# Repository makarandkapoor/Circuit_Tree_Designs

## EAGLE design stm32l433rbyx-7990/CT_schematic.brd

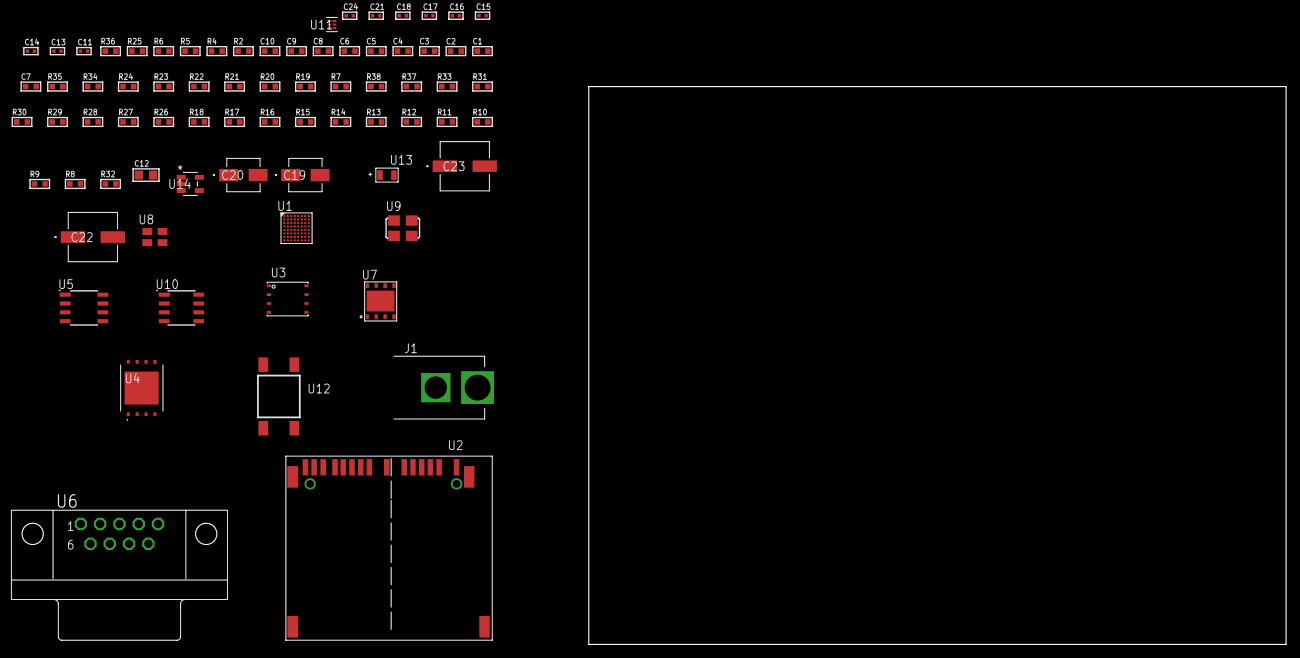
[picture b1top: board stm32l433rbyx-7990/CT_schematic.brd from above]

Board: 2 copper layers, 100.0 x 80.0 mm, 75 parts (0 on the bottom side), 47 nets, no tracks yet.

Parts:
C1, C9: 1e-06; C0603
C2, C3, C4, C5, C6, C10: 1e-07; C0603
C7: 4.7e-06; C0603
C8: 1e-08; C0603
C11, C15, C16, C21: 1e-07; C0402
C12: 1e-05; C0805
C13, C14, C17, C18, C24: 1e-08; C0402
C19: 1e-06; EXV-9B
C20: 2.2e-06; EXV-9B
C22, C23: 0.0001; EXV-9H
J1: PJ-037B; PJ-037B_PACKAGE
R2: 1000.0; R0603
R4: 4700.0; R0603
R5, R6: 2200.0; R0603
R7, R19, R20, R21, R22, R23, R24, R34, R35: 10000.0; R0603
R8, R9, R10, R11, R12, R13, R14, R15, R16, R17, R18, R27, R28, R29, R30, R31, R33: 100000.0; R0603
R25: 120.0; R0603
R26: 470000.0; R0603
R32: 164658.62; R0603
R36: 9100.0; R0603
R37: 680000.0; R0603
R38: 120000.0; R0603
U1: STM32L433RBY6; WLCSP64
U2: 10100565
U3: 24AA512-I/MF; DFN8-S
U4: S25FL128SDPNFI001; WNG008
U5: SN65HVD230D; SOIC-8
U6: 182-009-113R531; 182-009-MALE
U7: SST26VF032B-104I/MF; WFDN-8
U8: ASEK-32.768KHz-ECST; ASEK
U9: ASFL1-25MHZ-NCS; ASFL1
U10: LP2954AIMX/NOPB; LP2954
U11: TPS3895ADRYR; SON-6
U12: 4-1437565-2; SW_4-1437565-2
U13: Q65110A2395; LGM67K-G1J2-24-Z
U14: nc7sz125m5x; NC7SZ125M5X

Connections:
CLK_U1_C8: U1.C8, U8.3
CLK_U1_D8: U1.D8, U9.3
GND: C1.2, C2.2, C3.2, C4.2, C5.2, C6.2, C7.2, C8.2, C9.2, C10.2, C11.2, C12.2, C13.2, C14.2, C15.2, C16.2, C17.2, C18.2, C19.2, C20.2, C21.2, C22.2, C23.2, C24.2, J1.2, R2.2, R7.2, R20.2, R26.2, R33.2, R36.2, R38.2, U1.A7, U1.B1, U1.F8, U1.H2, U1.H8, U2.6, U2.10, U2.12, U2.16, U2.17, U2.20, U2.21, U3.4, U3.7, U4.4, U4.PAD, U5.2, U6.5, U7.4, U7.9, U8.2, U9.2, U10.4, U11.2, U13.C, U14.1, U14.3
NET_U1_A6: R6.1, U1.A6, U3.5
NET_U1_B5: R5.1, U1.B5, U3.6
NET_U1_C5: R7.1, U1.C5
NET_U1_D6: R4.1, U1.D6, U14.4
NET_U1_H4: U12.3, U12.4
NET_U2_1: R10.1, U2.1
NET_U2_2: R9.1, U2.2
NET_U2_18: U2.18, U2.19
NET_U3_1: R19.1, U3.1
NET_U3_2: R20.1, U3.2
NET_U3_3: R21.1, U3.3
NET_U4_3: R22.1, U4.3
NET_U4_7: R24.1, U4.7
NET_U5_6: R25.2, U5.6
NET_U5_8: R26.1, U5.8
NET_U6_2: R25.2, U5.6, U6.2
NET_U6_3: R25.1, U5.7, U6.3
NET_U10_3: R31.1, U10.3
NET_U10_5: R30.1, U10.5
NET_U10_7: R32.2, R33.1, U10.7
NET_U11_1: R35.1, R36.1, U11.1
NET_U11_3: R37.2, R38.1, U11.3
NET_U11_4: R34.1, U11.4, U14.2
NET_U12_1: R2.1, U12.1, U12.2
PROC_CAN1_RX: U1.D3, U5.4
PROC_CAN1_TX: U1.C1, U5.1
PROC_QUADSPI_BK1_IO0: U1.H5, U7.5
PROC_QUADSPI_BK1_IO1: U1.F4, U7.2
PROC_QUADSPI_BK1_IO2: R28.1, U1.H6, U7.3
PROC_QUADSPI_BK1_IO3: R29.1, U1.G5, U7.7
PROC_QUADSPI_BK1_NCS: R27.1, U1.F6, U7.1
PROC_QUADSPI_CLK: U1.G6, U7.6
PROC_SDMMC1_CK: R8.1, U1.A3, U2.8
PROC_SDMMC1_D0: R11.1, U1.F3, U2.4
PROC_SDMMC1_D1: R12.1, U1.E2, U2.3
PROC_SDMMC1_D2: R13.1, U1.C3, U2.15
PROC_SDMMC1_D3: R14.1, U1.B3, U2.14
PROC_SDMMC1_D4: R15.1, U1.C6, U2.13
PROC_SDMMC1_D5: R16.1, U1.B6, U2.11
PROC_SDMMC1_D6: R17.1, U1.F1, U2.7
PROC_SDMMC1_D7: R18.1, U1.E1, U2.5
PROC_SPI1_NSS: R23.1, U4.1
VCC_S1_6V4: C19.1, C22.1, C23.1, J1.1, R31.2, U10.8
VCC_TIER1_3V3: C1.1, C2.1, C3.1, C4.1, C5.1, C6.1, C7.1, C8.1, C9.1, C10.1, C11.1, C12.1, C13.1, C14.1, C15.1, C16.1, C17.1, C18.1, C20.1, C21.1, C24.1, R4.2, R5.2, R6.2, R8.2, R9.2, R10.2, R11.2, R12.2, R13.2, R14.2, R15.2, R16.2, R17.2, R18.2, R19.2, R21.2, R22.2, R23.2, R24.2, R27.2, R28.2, R29.2, R30.2, R32.1, R34.2, R35.2, R37.1, U1.A1, U1.A8, U1.B7, U1.G8, U1.H1, U1.H7, U2.9, U3.8, U4.8, U5.3, U7.8, U8.4, U9.4, U10.1, U11.6, U14.5

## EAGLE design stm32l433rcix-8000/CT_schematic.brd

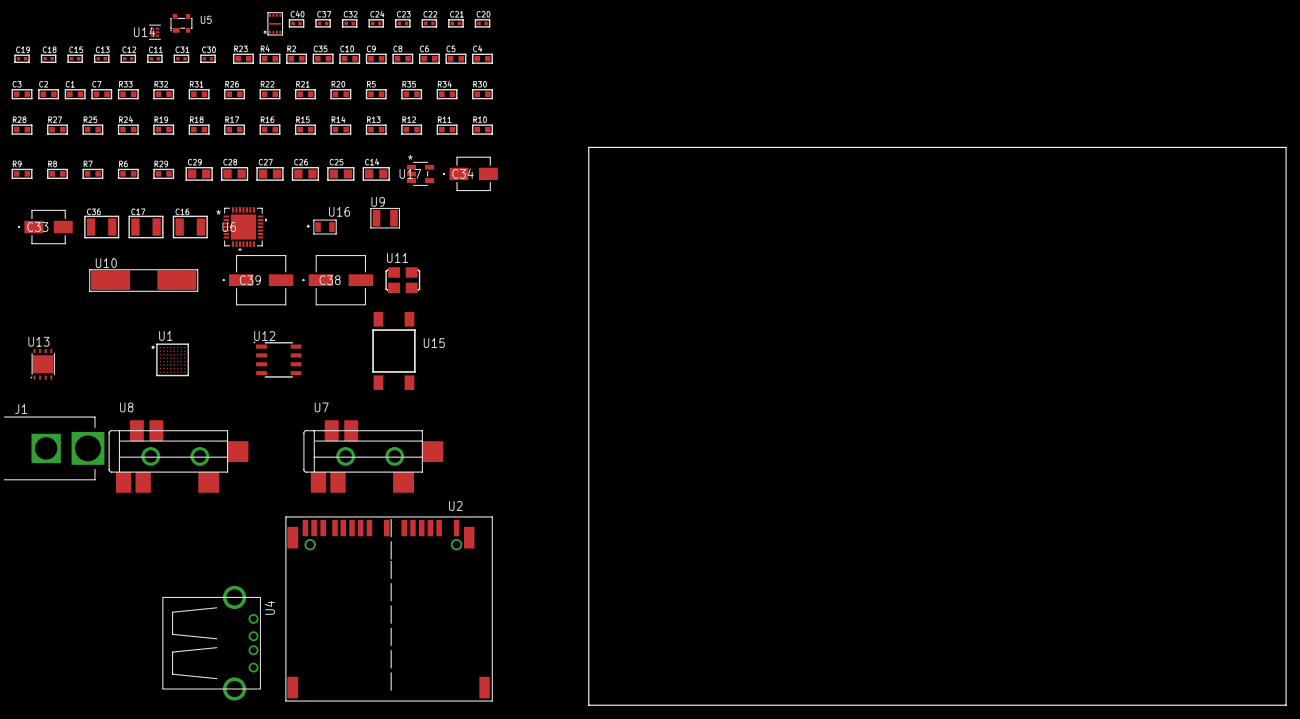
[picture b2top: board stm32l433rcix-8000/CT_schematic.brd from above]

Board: 2 copper layers, 100.0 x 80.0 mm, 91 parts (0 on the bottom side), 49 nets, no tracks yet.

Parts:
C1, C9, C35: 1e-06; C0603
C2, C3, C4, C5, C6, C10: 1e-07; C0603
C7: 4.7e-06; C0603
C8: 1e-08; C0603
C11, C12: 1e-11; C0402
C13, C15, C20, C21, C22, C23, C24, C37: 1e-07; C0402
C14, C25, C26, C27, C28, C29: 1e-05; C0805
C16, C17: 2.2e-05; C1210
C18, C19: 1e-09; C0402
C30, C31: 2.2e-11; C0402
C32, C40: 1e-08; C0402
C33: 1e-06; EXV-9B
C34: 2.2e-06; EXV-9B
C36: 1e-05; C1210
C38, C39: 0.0001; EXV-9H
J1: PJ-037B; PJ-037B_PACKAGE
R2: 1000.0; R0603
R4: 4700.0; R0603
R5, R31, R32: 10000.0; R0603
R6, R7, R8, R9, R10, R11, R12, R13, R14, R15, R16, R17, R18, R19, R24, R25, R27, R28, R30: 100000.0; R0603
R20, R21, R22, R26: 47000.0; R0603
R23: 680.0; R0603
R29: 153694.38; R0603
R33: 82000.0; R0603
R34: 300000.0; R0603
R35: 120000.0; R0603
U1: STM32L433RCI6; UFBGA64
U2: 10100565
U3: SST26WF080BT-104I/NP; USON-8
U4: 61400416021; USB-A-H
U5: prtr5v0u2ax; SOT143B
U6: WM8731CLSEFL; QFN-28
U7, U8: SJ-43515TS-SMT-TR
U9: ABS07-32.768KHZ-7-T
U10: ABLS-12.288MHZ-B4-T
U11: ASFL1-25MHZ-NCS; ASFL1
U12: LP2954AIMX/NOPB; LP2954
U13: LP2951ACSDX/NOPB; WSON-8
U14: TPS3895ADRYR; SON-6
U15: 4-1437565-2; SW_4-1437565-2
U16: Q65110A2395; LGM67K-G1J2-24-Z
U17: nc7sz125m5x; NC7SZ125M5X

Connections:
CLK_CRYSTAL_U1_A1: C11.1, U1.A1, U9.1
CLK_CRYSTAL_U1_B1: C12.1, U1.B1, U9.2
CLK_CRYSTAL_U6_1: C30.1, U6.1, U10.1
CLK_CRYSTAL_U6_2: C31.1, U6.2, U10.2
CLK_U1_C1: U1.C1, U11.3
GND: C1.2, C2.2, C3.2, C4.2, C5.2, C6.2, C7.2, C8.2, C9.2, C10.2, C11.2, C12.2, C13.2, C14.2, C15.2, C19.2, C20.2, C21.2, C22.2, C23.2, C24.2, C25.2, C26.2, C27.2, C28.2, C29.2, C30.2, C31.2, C32.2, C33.2, C34.2, C35.2, C36.2, C37.2, C38.2, C39.2, C40.2, J1.2, R2.2, R5.2, R20.2, R21.2, R22.2, R27.2, R30.2, R33.2, R35.2, U1.C2, U1.D4, U1.D5, U1.D6, U1.F1, U2.6, U2.10, U2.12, U2.16, U2.17, U2.20, U2.21, U3.4, U3.9, U4.4, U4.5, U4.6, U5.1, U6.4, U6.15, U6.19, U6.25, U6.26, U6.29, U7.1, U8.1, U11.2, U12.4, U13.3, U13.4, U13.PAD, U14.2, U16.C, U17.1, U17.3
NET_U1_B4: R5.1, U1.B4
NET_U1_E1: R4.1, U1.E1, U17.4
NET_U1_H8: U15.3, U15.4
NET_U2_1: R8.1, U2.1
NET_U2_2: R7.1, U2.2
NET_U2_18: U2.18, U2.19
NET_U5_4: U4.1, U5.4
NET_U6_20: C24.1, C29.1, U6.20
NET_U7_2: C17.1, R21.1, U7.2
NET_U7_5: C16.1, R20.1, U7.5
NET_U8_5: C18.1, C19.1, R22.1, R23.1, U8.5
NET_U12_3: R25.1, U12.3
NET_U12_5: R24.1, U12.5
NET_U12_7: R26.2, R27.1, U12.7
NET_U13_5: R28.1, U13.5
NET_U13_7: R29.2, R30.1, U13.7
NET_U14_1: R32.1, R33.1, U14.1
NET_U14_3: R34.2, R35.1, U14.3
NET_U14_4: R31.1, U14.4, U17.2
NET_U15_1: R2.1, U15.1, U15.2
PROC_QUADSPI_BK1_IO0: U1.G5, U3.5
PROC_QUADSPI_BK1_IO1: U1.F5, U3.2
PROC_QUADSPI_BK1_IO2: R18.1, U1.H4, U3.3
PROC_QUADSPI_BK1_IO3: R19.1, U1.G4, U3.7
PROC_QUADSPI_BK1_NCS: R17.1, U1.F3, U3.1
PROC_QUADSPI_CLK: U1.G3, U3.6
PROC_SAI1_FS_A: U1.C7, U6.9, U6.11
PROC_SAI1_SCK_A: U1.D7, U6.7
PROC_SAI1_SD_A: U1.C6, U6.8
PROC_SDMMC1_CK: R6.1, U1.C5, U2.8
PROC_SDMMC1_D0: R9.1, U1.E8, U2.4
PROC_SDMMC1_D1: R10.1, U1.D8, U2.3
PROC_SDMMC1_D2: R11.1, U1.B7, U2.15
PROC_SDMMC1_D3: R12.1, U1.B6, U2.14
PROC_SDMMC1_D4: R13.1, U1.B3, U2.13
PROC_SDMMC1_D5: R14.1, U1.A3, U2.11
PROC_SDMMC1_D6: R15.1, U1.F6, U2.7
PROC_SDMMC1_D7: R16.1, U1.E7, U2.5
PROC_USB_DM: U1.C8, U4.2, U5.3
PROC_USB_DP: U1.B8, U4.3, U5.2
VCC_S1_11V0: C33.1, C35.1, C38.1, C39.1, J1.1, R25.2, U12.8, U13.8
VCC_TIER1_1V8: C1.1, C2.1, C3.1, C4.1, C5.1, C6.1, C7.1, C13.1, C14.1, C15.1, C20.1, C21.1, C22.1, C23.1, C25.1, C26.1, C27.1, C28.1, C34.1, C37.1, C40.1, R4.2, R6.2, R7.2, R8.2, R9.2, R10.2, R11.2, R12.2, R13.2, R14.2, R15.2, R16.2, R17.2, R18.2, R19.2, R24.2, R26.1, R31.2, R32.2, R34.1, U1.B2, U1.D2, U1.E4, U1.E6, U2.9, U3.8, U6.3, U6.5, U6.12, U6.18, U12.1, U14.6, U17.5
VCC_TIER1_3V3: C8.1, C9.1, C10.1, C32.1, C36.1, R28.2, R29.1, U1.E5, U1.H1, U11.4, U13.1

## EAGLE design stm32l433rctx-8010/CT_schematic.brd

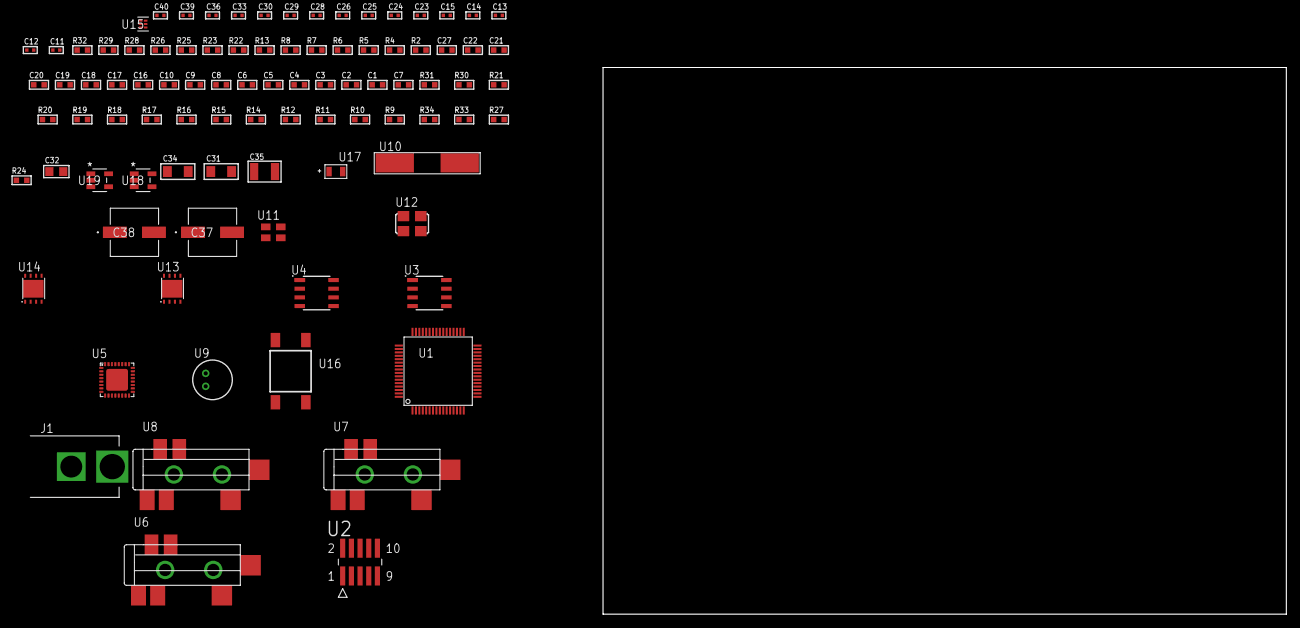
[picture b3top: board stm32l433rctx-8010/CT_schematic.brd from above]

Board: 2 copper layers, 100.0 x 80.0 mm, 92 parts (0 on the bottom side), 54 nets, no tracks yet.

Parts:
C1, C9, C16, C17, C18, C19, C20, C21, C22, C27: 1e-06; C0603
C2, C3, C4, C5, C6, C10: 1e-07; C0603
C7: 4.7e-06; C0603
C8: 1e-08; C0603
C11, C12: 1e-11; C0402
C13, C23, C24, C25, C26, C36: 1e-07; C0402
C14, C15, C28, C29, C30, C33, C39, C40: 1e-08; C0402
C31, C34: 1e-05; C1206
C32: 1e-05; C0805
C35: 1e-05; C1210
C37, C38: 0.0001; EXV-9H
J1: PJ-037B; PJ-037B_PACKAGE
R2, R26, R29: 1000.0; R0603
R4: 4700.0; R0603
R5, R6, R7, R8: 2200.0; R0603
R9, R10, R11, R12, R14, R15, R16, R17, R18, R19, R20, R21, R30, R31: 10000.0; R0603
R13: 5.0; R0603
R22, R23: 1270.0; R0603
R24, R27: 100000.0; R0603
R25: 200.0; R0603
R28: 2231.0; R0603
R32: 9100.0; R0603
R33: 680000.0; R0603
R34: 120000.0; R0603
U1: STM32L433RCT6; LQFP64
U2: FTSH-105-01-L-DV-K; SAMTEC_FTSH-105-01-L-DV-K
U3, U4: AT24C02D-SSHM-T; AT24C02D
U5: SGTL5000XNAA3; QFN-32
U6, U7, U8: SJ-43515TS-SMT-TR
U9: WM-64PCT; WM-64PC
U10: ABLS-25.000MHZ-B2F-T
U11: ASEK-32.768KHz-ECST; ASEK
U12: ASFL-24.57MHZ-NCS; ASFL1
U13, U14: LP3878SDX-ADJ/NOPB; WSON-8
U15: TPS3895ADRYR; SON-6
U16: 4-1437565-2; SW_4-1437565-2
U17: Q65110A2395; LGM67K-G1J2-24-Z
U18, U19: nc7sz125m5x; NC7SZ125M5X

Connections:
CLK_CRYSTAL_U1_5: C11.1, U1.5, U10.1
CLK_CRYSTAL_U1_6: C12.1, U1.6, U10.2
CLK_U1_3: U1.3, U11.3
CLK_U5_21: U5.21, U12.3
GND: C1.2, C2.2, C3.2, C4.2, C5.2, C6.2, C7.2, C8.2, C9.2, C10.2, C11.2, C12.2, C13.2, C14.2, C15.2, C23.2, C24.2, C25.2, C26.2, C27.2, C28.2, C29.2, C30.2, C31.2, C32.2, C33.2, C34.2, C35.2, C36.2, C37.2, C38.2, C39.2, C40.2, J1.2, R2.2, R9.2, R13.2, R14.2, R16.2, R17.2, R18.2, R20.2, R21.2, R23.2, R26.2, R29.2, R32.2, R34.2, U1.12, U1.18, U1.31, U1.47, U1.63, U2.3, U2.5, U3.4, U4.4, U5.1, U5.3, U5.7, U5.EXP, U7.1, U8.1, U9.2, U11.2, U12.2, U13.3, U13.PAD, U14.3, U14.PAD, U15.2, U17.C, U18.2, U18.3, U19.1, U19.3
NET_U1_7: R4.1, U1.7, U19.4
NET_U1_29: R7.1, U1.29, U4.6
NET_U1_30: R8.1, U1.30, U4.5
NET_U1_42: R5.1, U1.42, U3.6
NET_U1_43: R6.1, U1.43, U3.5
NET_U1_60: R9.1, U1.60
NET_U1_62: U16.3, U16.4
NET_U2_9: R13.1, U2.9
NET_U3_1: R15.1, U3.1
NET_U3_2: R16.1, U3.2
NET_U3_3: R17.1, U3.3
NET_U3_7: R14.1, U3.7
NET_U4_1: R19.1, U4.1
NET_U4_2: R20.1, U4.2
NET_U4_3: R21.1, U4.3
NET_U4_7: R18.1, U4.7
NET_U5_10: C26.1, U5.10
NET_U5_29: R22.1, U5.29
NET_U5_31: R23.1, U5.31
NET_U6_1: U5.4, U6.1
NET_U6_2: U5.2, U6.2
NET_U6_5: U5.6, U6.5
NET_U7_2: C17.1, U7.2
NET_U7_5: C16.1, U7.5
NET_U8_2: C19.1, C20.1, U8.2
NET_U8_5: C18.1, U8.5
NET_U8_13: C19.2, C20.2
NET_U9_1: C21.1, C22.1, C27.1, U5.16, U9.1
NET_U9_15: C21.2, C22.2
NET_U13_1: C30.1, U13.1
NET_U13_6: R25.2, R26.1, U13.6
NET_U13_8: R24.1, U13.8
NET_U14_1: C33.1, U14.1
NET_U14_6: R28.2, R29.1, U14.6
NET_U14_8: R27.1, U14.8
NET_U15_1: R31.1, R32.1, U15.1
NET_U15_3: R33.2, R34.1, U15.3
NET_U15_4: R30.1, U15.4, U18.4, U19.2
NET_U16_1: R2.1, U16.1, U16.2
PROC_SAI1_FS_A: U1.33, U5.23
PROC_SAI1_SCK_A: U1.34, U5.24
PROC_SAI1_SD_A: U1.11, U5.26
PROC_SYS_JTCK_SWCLK: R11.1, U1.49, U2.4
PROC_SYS_JTDO_SWO: U1.55, U2.6
PROC_SYS_JTMS_SWDIO: R12.1, U1.46, U2.2
RST_OUT_U2_JTAG_RST_B: R10.1, U2.10, U18.1
VCC_S1_10V8: C31.1, C34.1, C37.1, C38.1, J1.1, R24.2, R27.2, U13.4, U14.4
VCC_TIER1_1V2: C23.1, C32.1, R25.1, U5.30, U13.5
VCC_TIER1_3V3: C1.1, C2.1, C3.1, C4.1, C5.1, C6.1, C7.1, C8.1, C9.1, C10.1, C13.1, C14.1, C15.1, C24.1, C25.1, C28.1, C29.1, C35.1, C36.1, C39.1, C40.1, R4.2, R5.2, R6.2, R7.2, R8.2, R10.2, R11.2, R12.2, R15.2, R19.2, R22.2, R28.1, R30.2, R31.2, R33.1, U1.1, U1.13, U1.19, U1.32, U1.48, U1.64, U2.1, U3.8, U4.8, U5.5, U5.20, U11.4, U12.4, U14.5, U15.6, U18.5, U19.5

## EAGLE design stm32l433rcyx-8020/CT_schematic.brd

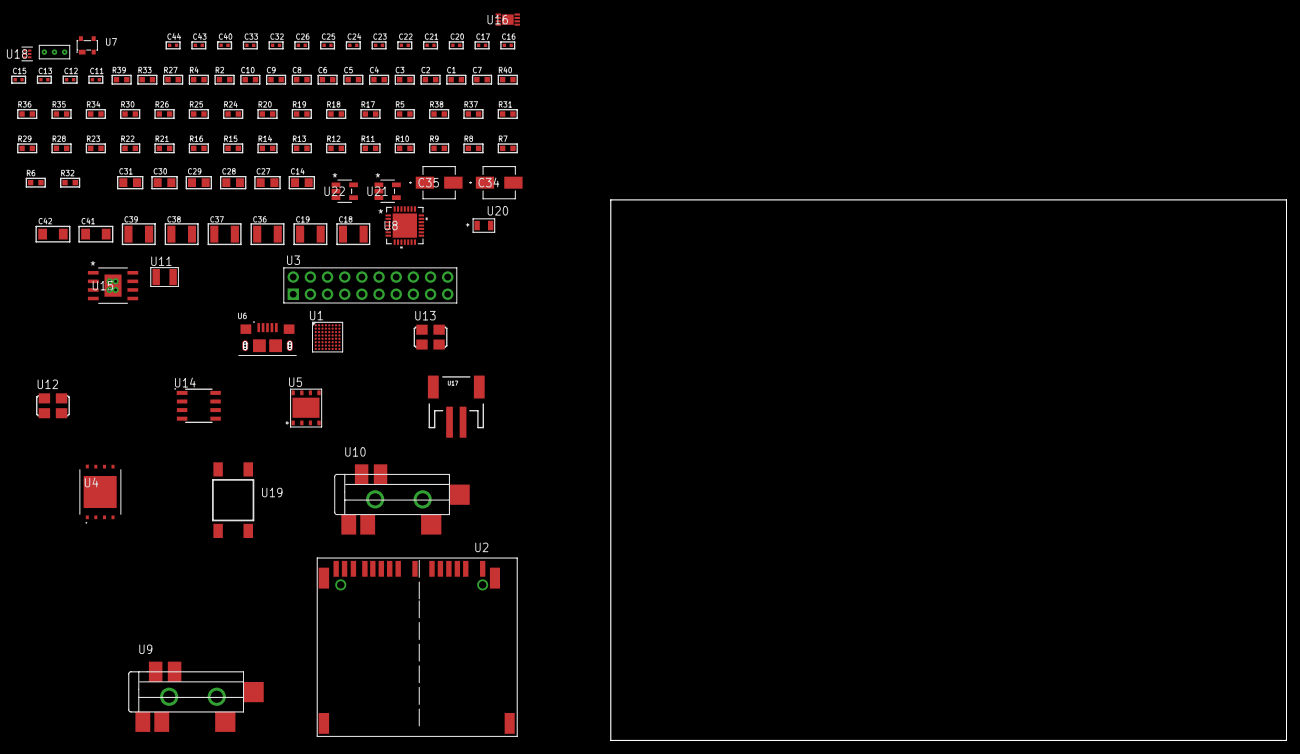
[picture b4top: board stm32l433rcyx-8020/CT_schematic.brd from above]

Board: 2 copper layers, 105 parts (0 on the bottom side), 61 nets, no tracks yet.

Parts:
C1, C9: 1e-06; C0603
C2, C3, C4, C5, C6, C10: 1e-07; C0603
C7: 4.7e-06; C0603
C8: 1e-08; C0603
C11, C12: 1e-11; C0402
C13, C15, C17, C22, C23, C24, C25, C26, C40: 1e-07; C0402
C14, C27, C28, C29, C30, C31: 1e-05; C0805
C16, C32, C33, C43, C44: 1e-08; C0402
C18, C19: 2.2e-05; C1210
C20, C21: 1e-09; C0402
C34: 1e-06; EXV-9B
C35: 2.2e-06; EXV-9B
C36, C37, C38, C39: 1e-05; C1210
C41, C42: 1e-05; C1206
R2: 1000.0; R0603
R4: 4700.0; R0603
R5, R17, R18, R19, R20, R34, R35, R40: 10000.0; R0603
R6, R7, R8, R9, R10, R11, R12, R13, R14, R15, R16, R21, R22, R23, R28, R29, R31: 100000.0; R0603
R24, R25, R26, R30: 47000.0; R0603
R27: 680.0; R0603
R32: 4031.5447154472; R0603
R33: 2200.0; R0603
R36: 82000.0; R0603
R37: 300000.0; R0603
R38: 120000.0; R0603
R39: 2000.0; R0603
U1: STM32L433RCY6; WLCSP64
U2: 10100565
U3: TST-110-05-T-D-RA
U4: S25FL128SDPNFI001; WNG008
U5: SST26WF016B-104I/MF; WFDN-8
U6: 10118193-0001LF; FCI_10118193-0001LF
U7: prtr5v0u2ax; SOT143B
U8: WM8731CLSEFL; QFN-28
U9, U10: SJ-43515TS-SMT-TR
U11: ABS07-32.768KHZ-7-T
U12: ASFL1-12.288MHZ-EC-T; ASFL1
U13: ASFL1-25MHZ-NCS; ASFL1
U14: LP2954AIMX/NOPB; LP2954
U15: MIC5234YME; SOIC-8_EP
U16: MCP73831T-2ACI/MC; DFN8_2X3MC
U17: S2B-PH-SM4-TB(LF)(SN); JST-2-SMD
U18: TPS3895ADRYR; SON-6
U19: 4-1437565-2; SW_4-1437565-2
U20: Q65110A2395; LGM67K-G1J2-24-Z
U21, U22: nc7sz125m5x; NC7SZ125M5X
U23: Dummy; DUMMY_PACKAGE_231

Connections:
CLK_CRYSTAL_U1_C7: C11.1, U1.C7, U11.1
CLK_CRYSTAL_U1_C8: C12.1, U1.C8, U11.2
CLK_U1_D8: U1.D8, U13.3
CLK_U8_1: U8.1, U12.3
GND: C1.2, C2.2, C3.2, C4.2, C5.2, C6.2, C7.2, C8.2, C9.2, C10.2, C11.2, C12.2, C13.2, C14.2, C15.2, C16.2, C17.2, C21.2, C22.2, C23.2, C24.2, C25.2, C26.2, C27.2, C28.2, C29.2, C30.2, C31.2, C32.2, C33.2, C34.2, C35.2, C36.2, C37.2, C38.2, C39.2, C40.2, C41.2, C42.2, C43.2, C44.2, R2.2, R5.2, R24.2, R25.2, R26.2, R31.2, R33.2, R36.2, R38.2, R39.2, U1.A7, U1.B1, U1.F8, U1.H2, U1.H8, U2.6, U2.10, U2.12, U2.16, U2.17, U2.20, U2.21, U3.4, U3.6, U3.8, U3.10, U3.12, U3.14, U3.16, U3.18, U3.20, U4.4, U4.PAD, U5.4, U5.9, U6.5, U6.6, U6.7, U6.8, U6.9, U7.1, U8.4, U8.15, U8.19, U8.25, U8.26, U8.29, U9.1, U10.1, U12.2, U13.2, U14.4, U15.7, U15.EPAD, U16.6, U16.9, U17.2, U18.2, U20.C, U21.2, U21.3, U22.1, U22.3, U23.1
INPUT_USBPOWER_5V: C41.1, R40.2, U6.1, U7.4, U16.1, U16.2
NET_U1_C5: R5.1, U1.C5
NET_U1_D6: R4.1, U1.D6, U22.4
NET_U1_H4: U19.3, U19.4
NET_U2_1: R8.1, U2.1
NET_U2_2: R7.1, U2.2
NET_U2_18: U2.18, U2.19
NET_U4_3: R18.1, U4.3
NET_U4_7: R20.1, U4.7
NET_U8_20: C26.1, C31.1, U8.20
NET_U9_2: C19.1, R25.1, U9.2
NET_U9_5: C18.1, R24.1, U9.5
NET_U10_5: C20.1, C21.1, R26.1, R27.1, U10.5
NET_U14_3: R29.1, U14.3
NET_U14_5: R28.1, U14.5
NET_U14_7: R30.2, R31.1, U14.7
NET_U15_4: R32.2, R33.1, U15.4
NET_U16_5: R40.1, U16.5
NET_U16_8: R39.1, U16.8
NET_U18_1: R35.1, R36.1, U18.1
NET_U18_3: R37.2, R38.1, U18.3
NET_U18_4: R34.1, U18.4, U21.4, U22.2
NET_U19_1: R2.1, U19.1, U19.2
PROC_PB7: U1.A6, U23.3
PROC_PD2: U1.A4, U23.2
PROC_QUADSPI_BK1_IO0: U1.H5, U5.5
PROC_QUADSPI_BK1_IO1: U1.F4, U5.2
PROC_QUADSPI_BK1_IO2: R22.1, U1.H6, U5.3
PROC_QUADSPI_BK1_IO3: R23.1, U1.G5, U5.7
PROC_QUADSPI_BK1_NCS: R21.1, U1.F6, U5.1
PROC_QUADSPI_CLK: U1.G6, U5.6
PROC_SAI1_FS_A: U1.D1, U8.9, U8.11
PROC_SAI1_SCK_A: U1.E3, U8.7
PROC_SAI1_SD_A: U1.D2, U8.8
PROC_SDMMC1_CK: R6.1, U1.A3, U2.8
PROC_SDMMC1_D0: R9.1, U1.F3, U2.4
PROC_SDMMC1_D1: R10.1, U1.E2, U2.3
PROC_SDMMC1_D2: R11.1, U1.C3, U2.15
PROC_SDMMC1_D3: R12.1, U1.B3, U2.14
PROC_SDMMC1_D4: R13.1, U1.C6, U2.13
PROC_SDMMC1_D5: R14.1, U1.B6, U2.11
PROC_SDMMC1_D6: R15.1, U1.F1, U2.7
PROC_SDMMC1_D7: R16.1, U1.E1, U2.5
PROC_SPI1_MISO: U1.B4, U4.2
PROC_SPI1_MOSI: U1.C4, U4.5
PROC_SPI1_NSS: R19.1, U1.A2, U4.1
PROC_SPI1_SCK: U1.F5, U4.6
PROC_SYS_JTCK_SWCLK: U1.B2, U3.9
PROC_SYS_JTDO_SWO: U1.A5, U3.13
PROC_SYS_JTMS_SWDIO: U1.C2, U3.7
PROC_USB_DM: U1.D3, U6.2, U7.3
PROC_USB_DP: U1.C1, U6.3, U7.2
RST_OUT_U3_SRESET_B: R17.1, U3.15, U21.1
VCC_S1_3V7: C34.1, C36.1, C37.1, C42.1, R29.2, U14.8, U15.5, U15.8, U16.3, U16.4, U17.1
VCC_TIER1_1V8: C1.1, C2.1, C3.1, C4.1, C5.1, C6.1, C7.1, C8.1, C9.1, C13.1, C14.1, C15.1, C16.1, C17.1, C22.1, C23.1, C24.1, C25.1, C27.1, C28.1, C29.1, C30.1, C35.1, C40.1, C43.1, C44.1, R4.2, R6.2, R7.2, R8.2, R9.2, R10.2, R11.2, R12.2, R13.2, R14.2, R15.2, R16.2, R17.2, R18.2, R19.2, R20.2, R21.2, R22.2, R23.2, R28.2, R30.1, R34.2, R35.2, R37.1, U1.A8, U1.B7, U1.G8, U1.H1, U1.H7, U2.9, U3.1, U4.8, U5.8, U8.3, U8.5, U8.12, U8.18, U14.1, U18.6, U21.5, U22.5
VCC_TIER1_3V3: C10.1, C32.1, C33.1, C38.1, C39.1, R32.1, U1.A1, U12.4, U13.4, U15.1

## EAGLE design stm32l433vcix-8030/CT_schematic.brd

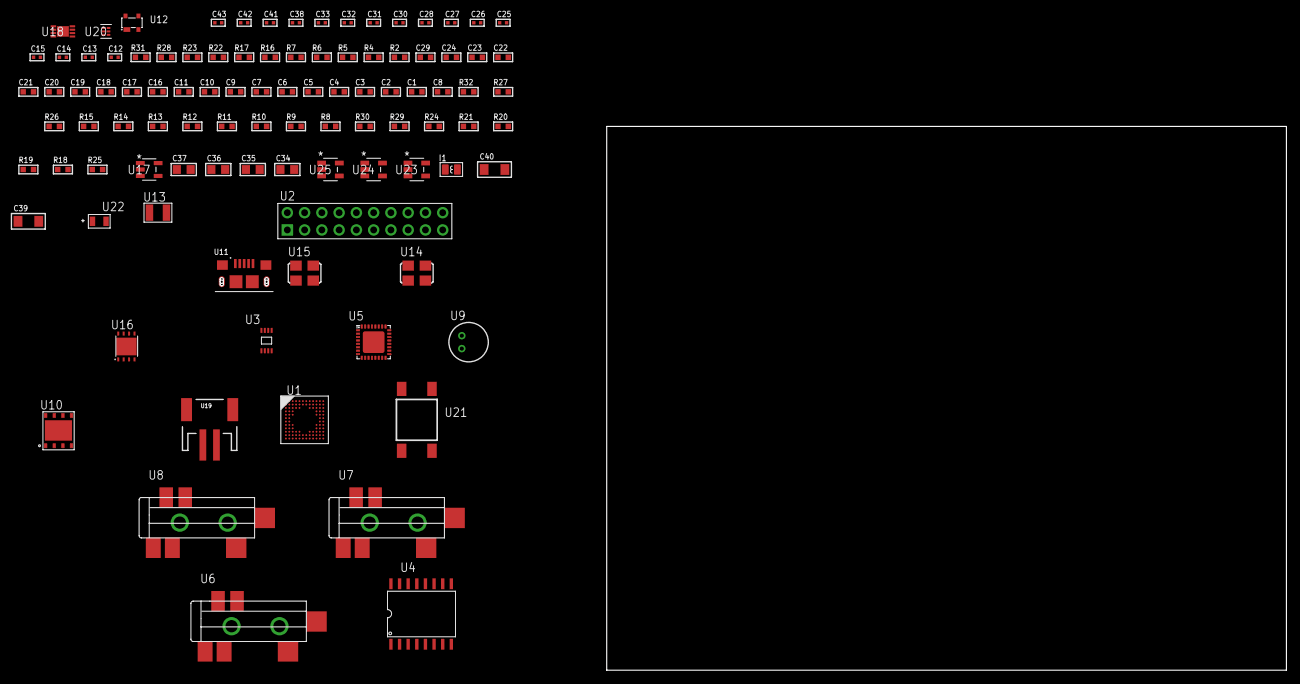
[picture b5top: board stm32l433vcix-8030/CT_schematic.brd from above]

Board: 2 copper layers, 99 parts (0 on the bottom side), 63 nets, no tracks yet.

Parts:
C1, C11, C16, C17, C18, C19, C20, C21, C22, C23, C24, C29: 1e-06; C0603
C2, C3, C4, C5, C6, C7, C9: 1e-07; C0603
C8: 4.7e-06; C0603
C10: 1e-08; C0603
C12, C13: 1e-11; C0402
C14, C25, C26, C27, C28, C30, C38: 1e-07; C0402
C15, C31, C32, C33, C41, C42, C43: 1e-08; C0402
C34, C35, C36, C37: 1e-05; C0805
C39, C40: 1e-05; C1206
I1: 1.5e-06; L0806
R2, R23: 1000.0; R0603
R4, R5: 4700.0; R0603
R6, R7: 2200.0; R0603
R8, R9, R10, R11, R12, R13, R14, R15, R26, R27, R32: 10000.0; R0603
R16, R17: 1270.0; R0603
R18, R19, R20, R21: 100000.0; R0603
R22: 200.0; R0603
R24: 220000.0; R0603
R25: 1000000.0; R0603
R28: 9100.0; R0603
R29: 680000.0; R0603
R30: 120000.0; R0603
R31: 2000.0; R0603
U1: STM32L433VCI6; UFBGA100
U2: TST-110-05-T-D-RA
U3: 24AA32AT-I/MNY; TDFN-8/6MM
U4: S25FL128SDSMFI000
U5: SGTL5000XNAA3; QFN-32
U6, U7, U8: SJ-43515TS-SMT-TR
U9: WM-64PCT; WM-64PC
U10: SST26VF064B-104I/MF; WFDN-8
U11: 10118193-0001LF; FCI_10118193-0001LF
U12: prtr5v0u2ax; SOT143B
U13: ABS07-32.768KHZ-7-T
U14: ASFL-24.57MHZ-NCS; ASFL1
U15: ASFL1-25MHZ-NCS; ASFL1
U16: LP3878SDX-ADJ/NOPB; WSON-8
U17: ltc3406es5; TSOT-23-5
U18: MCP73831T-2ACI/MC; DFN8_2X3MC
U19: S2B-PH-SM4-TB(LF)(SN); JST-2-SMD
U20: TPS3895ADRYR; SON-6
U21: 4-1437565-2; SW_4-1437565-2
U22: Q65110A2395; LGM67K-G1J2-24-Z
U23, U24, U25: nc7sz125m5x; NC7SZ125M5X

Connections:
CLK_CRYSTAL_U1_D1: C12.1, U1.D1, U13.1
CLK_CRYSTAL_U1_E1: C13.1, U1.E1, U13.2
CLK_U1_F1: U1.F1, U15.3
CLK_U5_21: U5.21, U14.3
GND: C1.2, C2.2, C3.2, C4.2, C5.2, C6.2, C7.2, C8.2, C9.2, C10.2, C11.2, C12.2, C13.2, C14.2, C15.2, C16.2, C17.2, C25.2, C26.2, C27.2, C28.2, C29.2, C30.2, C31.2, C32.2, C33.2, C34.2, C35.2, C36.2, C37.1, C37.2, C38.2, C39.2, C40.2, C41.2, C42.2, C43.2, R2.2, R8.2, R11.2, R12.2, R17.2, R23.2, R24.2, R28.2, R30.2, R31.2, U1.D3, U1.E3, U1.F2, U1.F11, U1.F12, U1.J1, U1.K1, U2.4, U2.6, U2.8, U2.10, U2.12, U2.14, U2.16, U2.18, U2.20, U3.4, U3.7, U4.10, U5.1, U5.3, U5.7, U5.EXP, U7.1, U8.1, U9.2, U10.4, U10.9, U11.5, U11.6, U11.7, U11.8, U11.9, U12.1, U14.2, U15.2, U16.3, U16.PAD, U17.2, U18.6, U18.9, U19.2, U20.2, U22.C, U23.2, U23.3, U24.1, U24.3, U25.1, U25.3
INPUT_USBPOWER_5V: C39.1, R32.2, U11.1, U12.4, U18.1, U18.2
NET_U1_A3: R6.1, U1.A3, U3.6
NET_U1_A4: R8.1, U1.A4
NET_U1_B3: R7.1, U1.B3, U3.5
NET_U1_H2: R5.1, U1.H2, U25.4
NET_U1_M12: U21.3, U21.4
NET_U3_1: R10.1, U3.1
NET_U3_2: R11.1, U3.2
NET_U3_3: R12.1, U3.3
NET_U4_3: R4.1, U4.3, U24.4
NET_U5_10: C28.1, U5.10
NET_U5_29: R16.1, U5.29
NET_U5_31: R17.1, U5.31
NET_U6_1: U5.4, U6.1
NET_U6_2: U5.2, U6.2
NET_U6_5: U5.6, U6.5
NET_U7_2: C19.1, U7.2
NET_U7_5: C18.1, U7.5
NET_U8_2: C21.1, C22.1, U8.2
NET_U8_5: C20.1, U8.5
NET_U8_13: C21.2, C22.2
NET_U9_1: C23.1, C24.1, C29.1, U5.16, U9.1
NET_U9_15: C23.2, C24.2
NET_U16_1: C33.1, U16.1
NET_U16_6: R22.2, R23.1, U16.6
NET_U16_8: R21.1, U16.8
NET_U17_3: I1.1, U17.3
NET_U17_5: R24.1, R25.1, U17.5
NET_U17_ATNET_3: I1.2, R25.2
NET_U18_5: R32.1, U18.5
NET_U18_8: R31.1, U18.8
NET_U20_1: R27.1, R28.1, U20.1
NET_U20_3: R29.2, R30.1, U20.3
NET_U20_4: R26.1, U20.4, U23.4, U24.2, U25.2
NET_U21_1: R2.1, U21.1, U21.2
PROC_QUADSPI_BK1_IO0: U1.L9, U10.5
PROC_QUADSPI_BK1_IO1: U1.M5, U10.2
PROC_QUADSPI_BK1_IO2: R19.1, U1.M4, U10.3
PROC_QUADSPI_BK1_IO3: R20.1, U1.L4, U10.7
PROC_QUADSPI_BK1_NCS: R18.1, U1.K3, U10.1
PROC_QUADSPI_BK2_IO0: U1.B7, U4.15
PROC_QUADSPI_BK2_IO1: U1.A6, U4.8
PROC_QUADSPI_BK2_IO2: R14.1, U1.B6, U4.9
PROC_QUADSPI_BK2_IO3: R15.1, U1.A5, U4.1
PROC_QUADSPI_BK2_NCS: R13.1, U1.B8, U4.7
PROC_QUADSPI_CLK: U1.L3, U1.L8, U4.16, U10.6
PROC_SAI1_FS_A: U1.B1, U5.23
PROC_SAI1_SCK_A: U1.C2, U5.24
PROC_SAI1_SD_A: U1.C12, U5.26
PROC_SYS_JTCK_SWCLK: U1.A10, U2.9
PROC_SYS_JTDO_SWO: U1.A8, U2.13
PROC_SYS_JTMS_SWDIO: U1.A11, U2.7
PROC_USB_DM: U1.B12, U11.2, U12.3
PROC_USB_DP: U1.A12, U11.3, U12.2
RST_OUT_U2_SRESET_B: R9.1, U2.15, U23.1
VCC_S1_3V7: C34.1, C36.1, C40.1, R21.2, U16.4, U17.4, U18.3, U18.4, U19.1
VCC_TIER1_1V2: C25.1, C35.1, R22.1, U5.30, U16.5
VCC_TIER1_3V3: C1.1, C2.1, C3.1, C4.1, C5.1, C6.1, C7.1, C8.1, C9.1, C10.1, C11.1, C14.1, C15.1, C16.1, C17.1, C26.1, C27.1, C30.1, C31.1, C32.1, C37.2, C38.1, C41.1, C42.1, C43.1, I1.2, R4.2, R5.2, R6.2, R7.2, R9.2, R10.2, R13.2, R14.2, R15.2, R16.2, R18.2, R19.2, R20.2, R25.2, R26.2, R27.2, R29.1, U1.C4, U1.C11, U1.E2, U1.G2, U1.G11, U1.G12, U1.H3, U1.L1, U1.M1, U2.1, U3.8, U4.2, U4.14, U5.5, U5.20, U10.8, U14.4, U15.4, U20.6, U23.5, U24.5, U25.5

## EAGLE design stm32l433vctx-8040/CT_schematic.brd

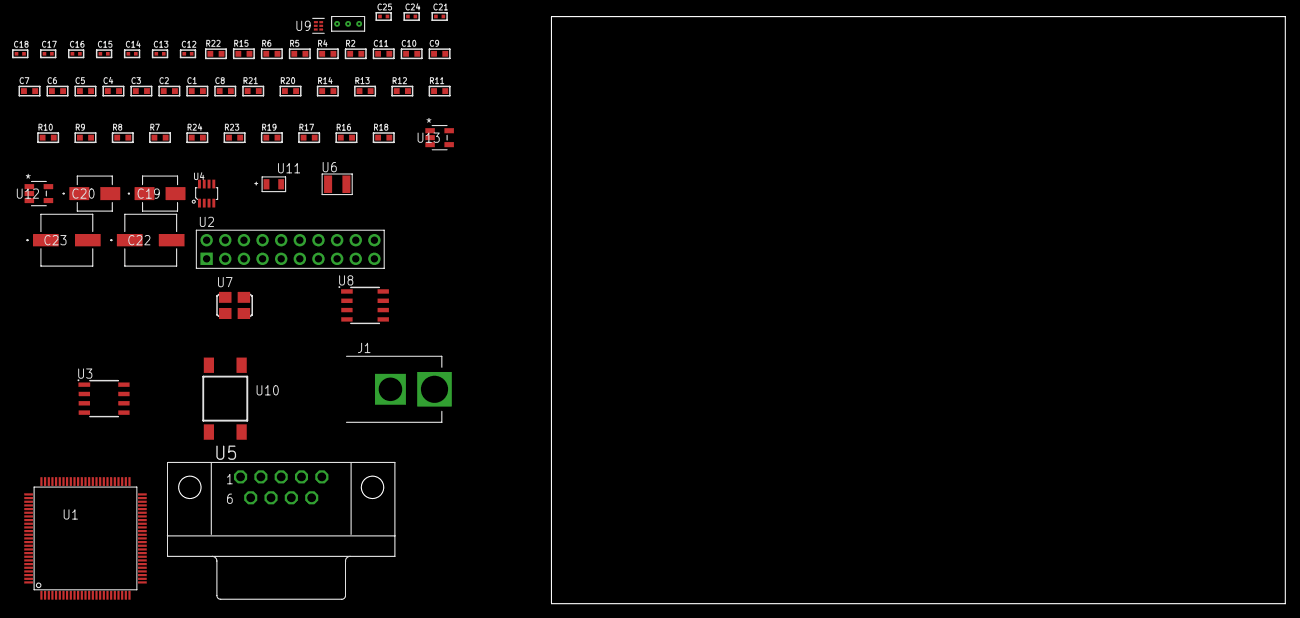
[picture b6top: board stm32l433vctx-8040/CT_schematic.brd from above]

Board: 2 copper layers, 100.0 x 80.0 mm, 62 parts (0 on the bottom side), 33 nets, no tracks yet.

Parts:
C1, C11: 1e-06; C0603
C2, C3, C4, C5, C6, C7, C9: 1e-07; C0603
C8: 4.7e-06; C0603
C10: 1e-08; C0603
C12, C13: 1e-11; C0402
C14, C15, C17, C21: 1e-07; C0402
C16, C18, C24, C25: 1e-08; C0402
C19: 1e-06; EXV-9B
C20: 2.2e-06; EXV-9B
C22, C23: 0.0001; EXV-9H
J1: PJ-037B; PJ-037B_PACKAGE
R2: 1000.0; R0603
R4: 4700.0; R0603
R5, R6: 2200.0; R0603
R7, R8, R9, R10, R11, R12, R13, R14, R20, R21: 10000.0; R0603
R15: 120.0; R0603
R16, R17, R19: 100000.0; R0603
R18: 164658.62; R0603
R22: 9100.0; R0603
R23: 680000.0; R0603
R24: 120000.0; R0603
U1: STM32L433VCT6; LQFP100
U2: TST-110-05-T-D-RA
U3: M24M02-DRMN6TP; SOIC-8
U4: MAX3051EKA+T; SOT-23-8
U5: 182-009-113R531; 182-009-MALE
U6: ABS07-32.768KHZ-7-T
U7: ASFL1-25MHZ-NCS; ASFL1
U8: LP2954AIMX/NOPB; LP2954
U9: TPS3895ADRYR; SON-6
U10: 4-1437565-2; SW_4-1437565-2
U11: Q65110A2395; LGM67K-G1J2-24-Z
U12, U13: nc7sz125m5x; NC7SZ125M5X
U14: Dummy; DUMMY_PACKAGE_138

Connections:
CLK_CRYSTAL_U1_8: C12.1, U1.8, U6.1
CLK_CRYSTAL_U1_9: C13.1, U1.9, U6.2
CLK_U1_12: U1.12, U7.3
GND: C1.2, C2.2, C3.2, C4.2, C5.2, C6.2, C7.2, C8.2, C9.2, C10.2, C11.2, C12.2, C13.2, C14.2, C15.2, C16.2, C17.2, C18.2, C19.2, C20.2, C21.2, C22.2, C23.2, C24.2, C25.2, J1.2, R2.2, R7.2, R13.2, R14.2, R19.2, R22.2, R24.2, U1.10, U1.19, U1.20, U1.27, U1.49, U1.74, U1.99, U2.4, U2.6, U2.8, U2.10, U2.12, U2.14, U2.16, U2.18, U2.20, U3.4, U4.2, U4.8, U5.5, U7.2, U8.4, U9.2, U11.C, U12.2, U12.3, U13.1, U13.3, U14.1
NET_U1_14: R4.1, U1.14, U13.4
NET_U1_68: R5.1, U1.68, U3.6
NET_U1_69: R6.1, U1.69, U3.5
NET_U1_94: R7.1, U1.94
NET_U1_98: U10.3, U10.4
NET_U2_19: R13.1, U2.19
NET_U3_3: R14.1, U3.3
NET_U4_6: R15.2, U4.6
NET_U5_2: R15.2, U4.6, U5.2
NET_U5_3: R15.1, U4.7, U5.3
NET_U8_3: R17.1, U8.3
NET_U8_5: R16.1, U8.5
NET_U8_7: R18.2, R19.1, U8.7
NET_U9_1: R21.1, R22.1, U9.1
NET_U9_3: R23.2, R24.1, U9.3
NET_U9_4: R20.1, U9.4, U12.4, U13.2
NET_U10_1: R2.1, U10.1, U10.2
PROC_CAN1_RX: U1.70, U4.4
PROC_CAN1_TX: U1.71, U4.1
PROC_SYS_JTDI: R9.1, U1.77, U2.5
PROC_SYS_JTDO_SWO: U1.89, U2.13
PROC_SYS_JTMS_SWDIO: R10.1, U1.72, U2.7
PROC_SYS_JTRST: R8.1, U1.90, U2.3
PROC_SYS_TRACECLK: R11.1, U1.1, U2.9
PROC_TIM1_CH2: U1.42, U14.2
PROC_TIM1_CH4: U1.45, U14.3
RST_OUT_U2_SRESET_B: R12.1, U2.15, U12.1
VCC_S1_6V6: C19.1, C22.1, C23.1, J1.1, R17.2, U8.8
VCC_TIER1_3V3: C1.1, C2.1, C3.1, C4.1, C5.1, C6.1, C7.1, C8.1, C9.1, C10.1, C11.1, C14.1, C15.1, C16.1, C17.1, C18.1, C20.1, C21.1, C24.1, C25.1, R4.2, R5.2, R6.2, R8.2, R9.2, R10.2, R11.2, R12.2, R16.2, R18.1, R20.2, R21.2, R23.1, U1.6, U1.11, U1.21, U1.22, U1.28, U1.50, U1.73, U1.75, U1.100, U2.1, U2.2, U3.8, U4.3, U7.4, U8.1, U9.6, U12.5, U13.5

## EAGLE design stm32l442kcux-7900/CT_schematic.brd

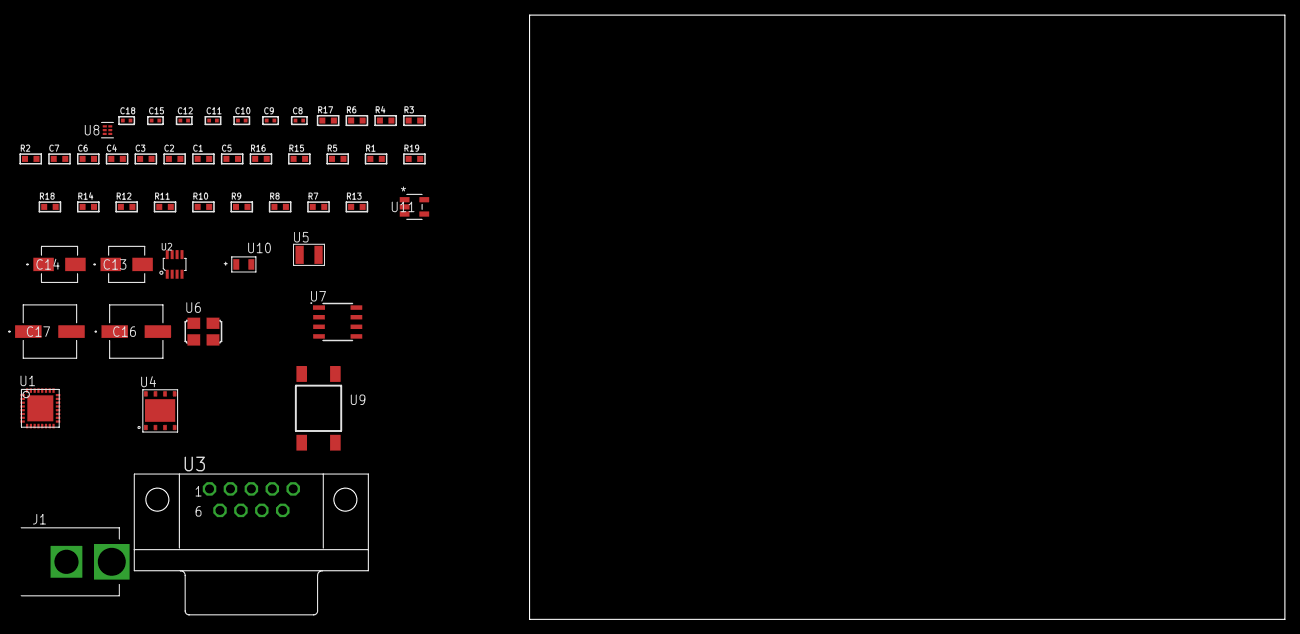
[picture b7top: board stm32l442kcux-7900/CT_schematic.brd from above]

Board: 2 copper layers, 100.0 x 80.0 mm, 49 parts (0 on the bottom side), 28 nets, no tracks yet.

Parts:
C1, C2, C3, C4: 1e-07; C0603
C5: 4.7e-06; C0603
C6: 1e-08; C0603
C7: 1e-06; C0603
C8, C9: 1e-11; C0402
C10, C11, C15: 1e-07; C0402
C12, C18: 1e-08; C0402
C13: 1e-06; EXV-9B
C14: 2.2e-06; EXV-9B
C16, C17: 0.0001; EXV-9H
J1: PJ-037B; PJ-037B_PACKAGE
R1, R5, R15, R16: 10000.0; R0603
R2: 1000.0; R0603
R3: 1600.5; R0603
R4: 4700.0; R0603
R6: 120.0; R0603
R7, R8, R9, R10, R11, R12, R14: 100000.0; R0603
R13: 164658.62; R0603
R17: 9100.0; R0603
R18: 680000.0; R0603
R19: 120000.0; R0603
U1: STM32L442KCUx; UFQFPN32
U2: MAX3051EKA+T; SOT-23-8
U3: 182-009-113R531; 182-009-MALE
U4: SST26VF016B-104I/MF; WFDN-8
U5: ABS07-32.768KHZ-7-T
U6: ASFL1-12MHZ-NCS; ASFL1
U7: LP2954AIMX/NOPB; LP2954
U8: TPS3895ADRYR; SON-6
U9: 4-1437565-2; SW_4-1437565-2
U10: Q65110A2395; LGM67K-G1J2-24-Z
U11: nc7sz125m5x; NC7SZ125M5X

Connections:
CLK_CRYSTAL_U1_2: C8.1, U1.2, U5.1
CLK_CRYSTAL_U1_3: C9.1, U1.3, U5.2
CLK_U1_6: U1.6, U6.3
GND: C1.2, C2.2, C3.2, C4.2, C5.2, C6.2, C7.2, C8.2, C9.2, C10.2, C11.2, C12.2, C13.2, C14.2, C15.2, C16.2, C17.2, C18.2, J1.2, R2.2, R5.2, R7.2, R14.2, R17.2, R19.2, U1.16, U1.32, U1.EPAD, U2.2, U3.5, U4.4, U4.9, U6.2, U7.4, U8.2, U10.C, U11.1, U11.3
NET_U1_4: R4.1, U1.4, U11.4
NET_U1_30: R3.1, U1.30, U10.A
NET_U1_31: R1.1, R5.1, U1.31, U9.3, U9.4
NET_U2_6: R6.2, U2.6
NET_U2_8: R7.1, U2.8
NET_U3_2: R6.2, U2.6, U3.2
NET_U3_3: R6.1, U2.7, U3.3
NET_U7_3: R12.1, U7.3
NET_U7_5: R11.1, U7.5
NET_U7_7: R13.2, R14.1, U7.7
NET_U8_1: R16.1, R17.1, U8.1
NET_U8_3: R18.2, R19.1, U8.3
NET_U8_4: R15.1, U8.4, U11.2
NET_U9_1: R2.1, U9.1, U9.2
PROC_CAN1_RX: U1.21, U2.4
PROC_CAN1_TX: U1.22, U2.1
PROC_QUADSPI_BK1_IO0: U1.15, U4.5
PROC_QUADSPI_BK1_IO1: U1.14, U4.2
PROC_QUADSPI_BK1_IO2: R9.1, U1.13, U4.3
PROC_QUADSPI_BK1_IO3: R10.1, U1.12, U4.7
PROC_QUADSPI_BK1_NCS: R8.1, U1.8, U4.1
PROC_QUADSPI_CLK: U1.9, U4.6
VCC_S1_8V1: C13.1, C16.1, C17.1, J1.1, R12.2, U7.8
VCC_TIER1_3V3: C1.1, C2.1, C3.1, C4.1, C5.1, C6.1, C7.1, C10.1, C11.1, C12.1, C14.1, C15.1, C18.1, R1.2, R3.2, R4.2, R8.2, R9.2, R10.2, R11.2, R13.1, R15.2, R16.2, R18.1, U1.1, U1.5, U1.17, U2.3, U4.8, U6.4, U7.1, U8.6, U11.5
